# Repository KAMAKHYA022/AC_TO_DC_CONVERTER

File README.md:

# AC to DC Converter PCB Project

## 1. Introduction

  Electrical power is supplied in two main forms: Alternating Current (AC) and Direct Current (DC). Understanding these two types of currents is essential before diving into the AC to DC conversion 
  process.

##  What is AC (Alternating Current)?

   AC is an electrical current that periodically reverses direction. It is commonly used for power transmission and is the type of electricity supplied to homes and industries. The voltage of AC varies 
   sinusoidally with time.

##  What is DC (Direct Current)?

   DC is a unidirectional flow of electric charge. It is used in batteries, electronic circuits, and low-voltage applications like mobile phones, laptops, and embedded systems.

## 2. What is an AC to DC Converter?

   An AC to DC Converter is an electronic circuit that converts AC voltage into DC voltage. This is necessary because many electronic devices operate on DC power, but electrical grids provide AC power.

## Why is AC to DC Conversion Required?

  Most electronic circuits require a stable DC supply.

  AC is more efficient for long-distance transmission, but DC is needed for circuits and devices.

  Batteries and microcontrollers work on DC power.

## 3. Types of AC to DC Converters

  There are several types of AC to DC converters based on their design and working principle:

  Half-Wave Rectifier – Uses a single diode, converts only half of the AC waveform.

  Full-Wave Rectifier – Uses two diodes or a bridge rectifier to convert both halves of the AC waveform.

  Bridge Rectifier – Uses four diodes to provide full-wave rectification with better efficiency.

## 4. Designing a 12V AC to DC Converter

  For this project, we design a 12V AC to DC Converter using KiCad for schematic and PCB design. The circuit includes a transformer, full-wave rectifier, smoothing capacitor, voltage regulator, and LED 
  indicator.

  Components Used:

  Transformer (X1) – Steps down 220V AC to 12V AC.

  Bridge Rectifier (D1-D4, 1N4007 diodes) – Converts AC to pulsating DC.

  Capacitor (C1, 1000µF) – Smooths the pulsating DC.

  Voltage Regulator (U1, 7812 IC) – Provides a steady 12V DC output.

  Resistors (R1, R2) – Current limiting resistors for circuit protection.

  LED Indicator (D5) – Shows power status.

## 5. PCB Design in KiCad

  The schematic is designed in KiCad, ensuring correct component placement and PCB layout. The PCB layout is optimized to minimize noise and improve efficiency.
## Designing a 12V AC to DC Converter

### Schematic Design in KiCad

### PCB Layout

### PCB 3D View

### Simulation in Proteus

## 6. Simulation in Proteus

To verify circuit functionality before manufacturing, the schematic is simulated in Proteus:

Transformer steps down 220V AC to 12V AC.

Bridge rectifier converts AC to DC.

Capacitor smooths the DC voltage.

IC 7812 ensures a regulated 12V DC output.

LED indicates circuit operation.

## 7. Why These Components Were Chosen?

7812 Voltage Regulator – Provides a steady 12V DC output with overvoltage protection.

1000µF Capacitor – Smooths rectified DC to reduce ripple.

10Ω Resistor (R2) – Helps with voltage stabilization.

2.2kΩ Resistor (R1) with LED – Limits current to the LED for indicating circuit operation.

## 8. Conclusion

This AC to DC converter provides a regulated 12V DC output from 220V AC input. The design ensures efficiency and reliability for powering various electronics. The project demonstrates PCB design, simulation, and implementation of a real-world power supply circuit.

Future Improvements:

Adding a heat sink to the 7812 regulator for better thermal management.

Designing a dual-output version for 5V and 12V DC supplies.

Implementing a switching regulator for better efficiency.

Tools Used:

✅ KiCad – Schematic & PCB Design
✅ Proteus – Circuit Simulation

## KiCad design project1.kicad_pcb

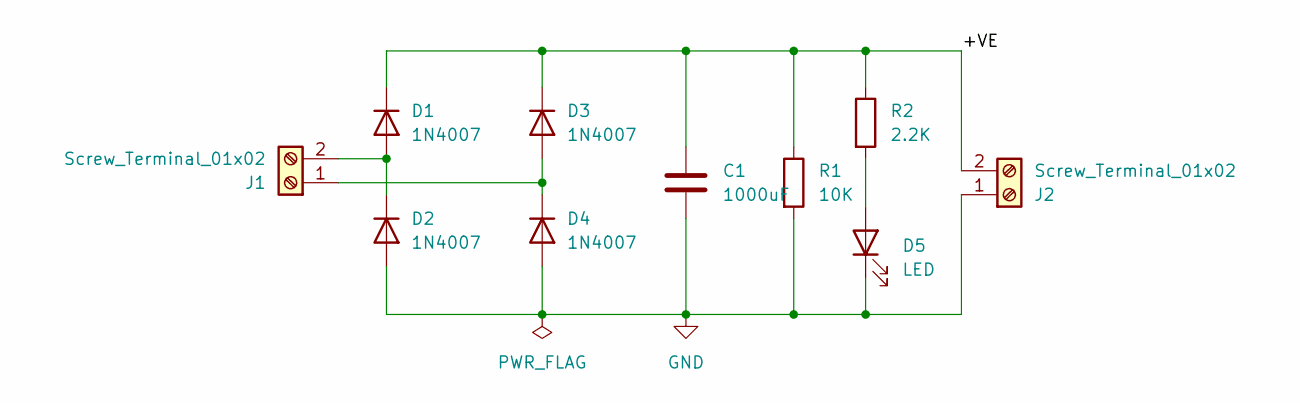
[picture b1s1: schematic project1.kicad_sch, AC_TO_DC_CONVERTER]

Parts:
C1: 1000uF; C_Radial_D8.0mm_H11.5mm_P3.50mm
D1, D2, D3, D4: 1N4007; D_DO-41_SOD81_P10.16mm_Horizontal
D5: LED; LED_D5.0mm
J1, J2: Screw_Terminal_01x02; TerminalBlock_bornier-2_P5.08mm
R1: 10K; R_Axial_DIN0204_L3.6mm_D1.6mm_P7.62mm_Horizontal
R2: 2.2K; R_Axial_DIN0204_L3.6mm_D1.6mm_P7.62mm_Horizontal

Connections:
/+VE: C1.1, D1.1 (K), D3.1 (K), J2.2, R1.1, R2.1; also elsewhere on the board
GND: C1.2, D2.2 (A), D4.2 (A), D5.1 (K), J2.1, R1.2; also elsewhere on the board
unnamed: D1.2 (A), D2.1 (K), J1.2
unnamed: D3.2 (A), D4.1 (K), J1.1
unnamed: D5.2 (A), R2.2

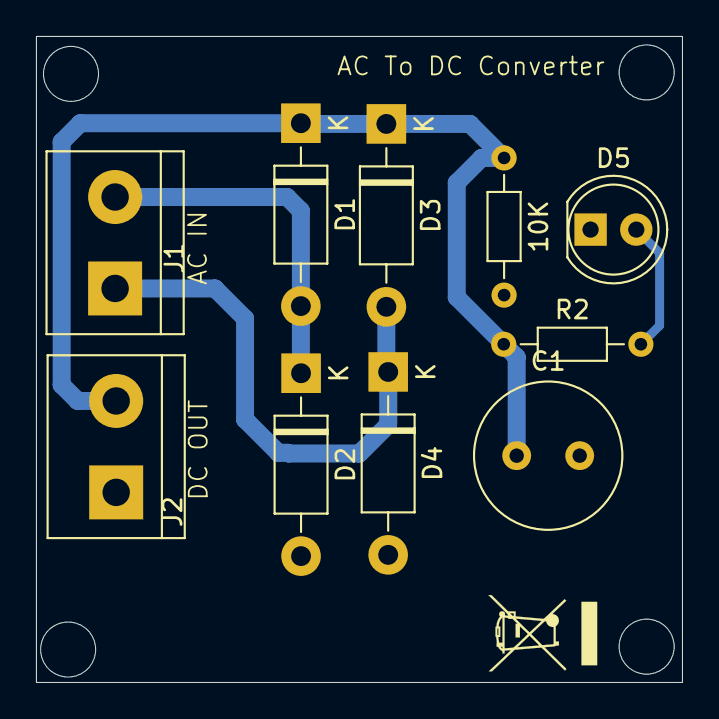
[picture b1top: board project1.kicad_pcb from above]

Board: 2 copper layers, 35.9 x 35.9 mm, 10 parts (0 on the bottom side), 5 nets.

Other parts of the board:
10K: R; R_Axial_DIN0204_L3.6mm_D1.6mm_P7.62mm_Horizontal

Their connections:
/+VE: 10K.1; also elsewhere on the board
GND: 10K.2; also elsewhere on the board

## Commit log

2025-02-08 ac-to-dc_converter
